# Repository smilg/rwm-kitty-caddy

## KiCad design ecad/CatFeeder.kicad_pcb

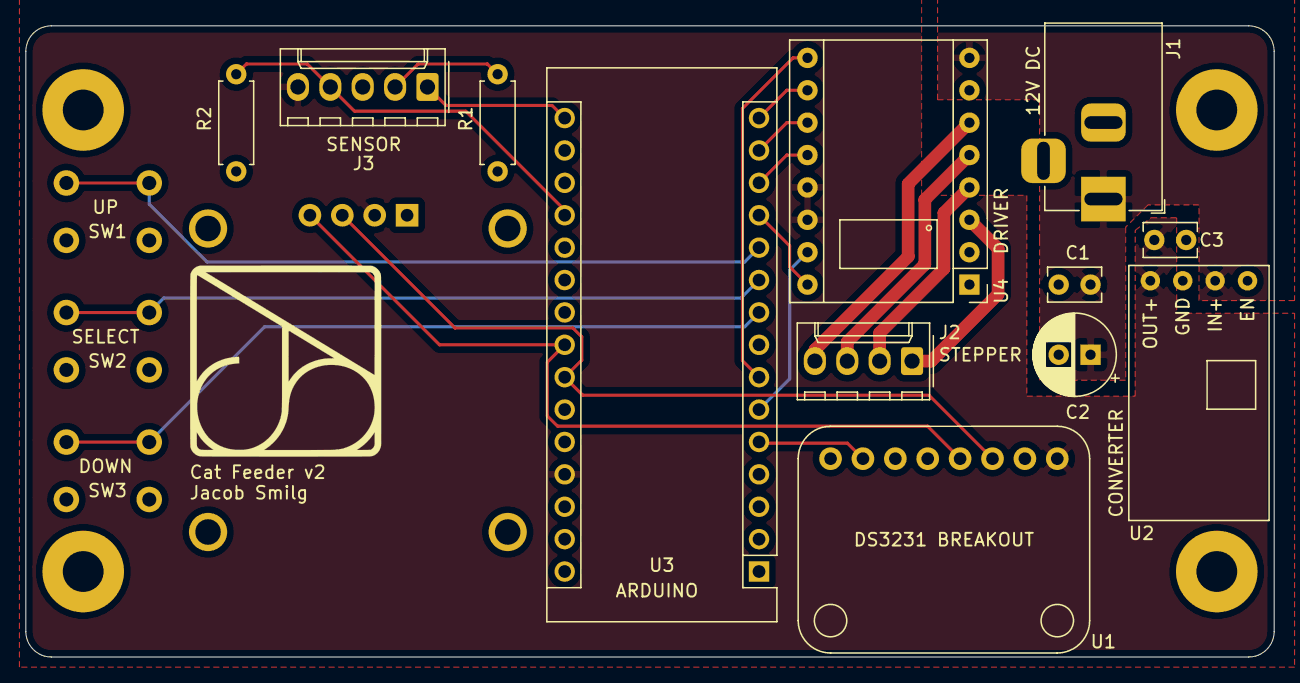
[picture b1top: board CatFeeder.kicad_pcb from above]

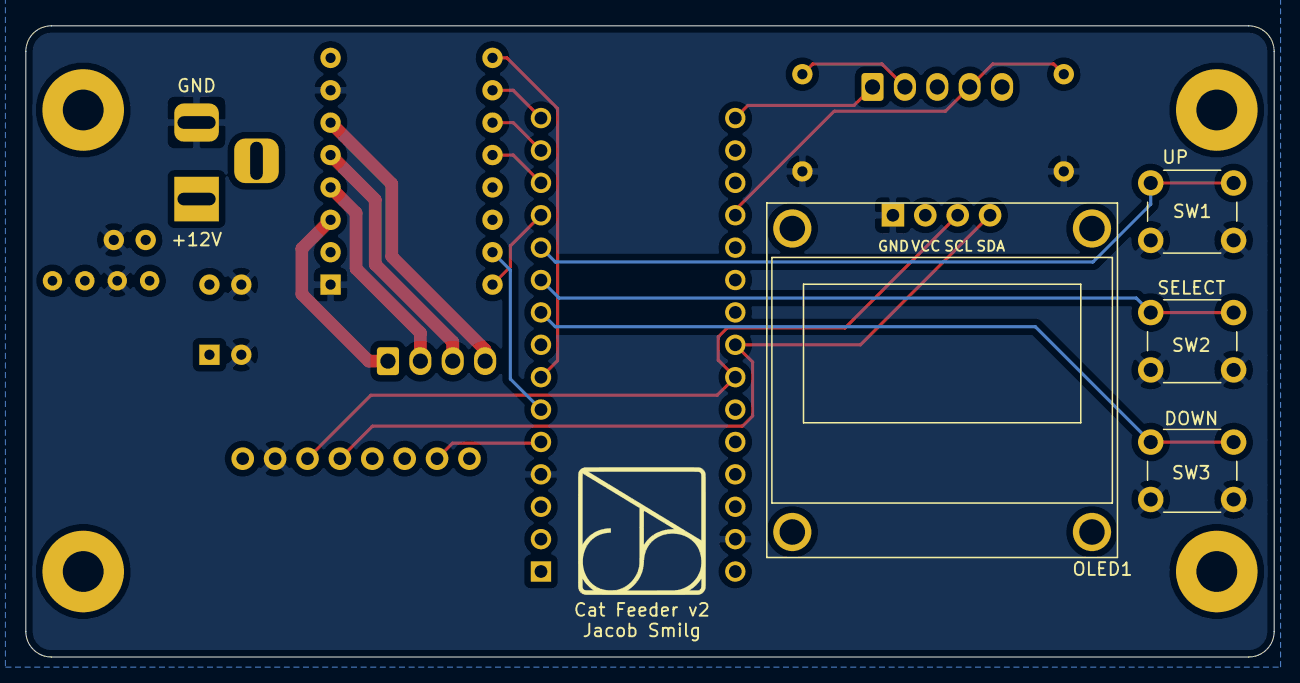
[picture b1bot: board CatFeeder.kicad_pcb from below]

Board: 2 copper layers, 97.9 x 49.5 mm, 16 parts (4 on the bottom side), 22 nets.

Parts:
C1, C3: 0.1μF; C_Rect_L4.0mm_W2.5mm_P2.50mm
C2: 100μF; CP_Radial_D6.3mm_P2.50mm
J1: Barrel_Jack; BarrelJack_Horizontal
J2: STEPPER; Molex_KK-254_AE-6410-04A_1x04_P2.54mm_Vertical
J3: OP740WZ; Molex_KK-254_AE-6410-05A_1x05_P2.54mm_Vertical
OLED1: I2COLEDDisplay; i2cOLED
R1: 100Ω; R_Axial_DIN0207_L6.3mm_D2.5mm_P7.62mm_Horizontal
R2: 100KΩ; R_Axial_DIN0207_L6.3mm_D2.5mm_P7.62mm_Horizontal
SW1: UP; SW_PUSH_6mm
SW2: SELECT; SW_PUSH_6mm
SW3: DOWN; SW_PUSH_6mm
U1: DS3231 BREAKOUT; DS3231Breakout
U2: BuckConverter; BuckConverterBreakout
U3: Arduino_Nano_v3.x; Arduino_Nano
U4: DRV8825; DRV8825Breakout

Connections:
1HZ_INT: U1.7, U3.5
+5V: C3.1, J3.5, OLED1.2, U1.1, U2.1, U3.27, U4.13, U4.14
+12V: C1.1, C2.1, J1.1, U2.3, U4.8
DIR: U3.12, U4.16
DOWN: SW3.2, U3.9
GND: C1.2, C2.2, C3.2, J1.2, OLED1.1, R1.2, R2.2, SW1.1, SW2.1, SW3.1, U1.2, U2.2, U3.4, U3.29, U4.1, U4.7
M0: U3.15, U4.10
M1: U3.14, U4.11
M2: U3.13, U4.12
unnamed: J2.1, U4.3
unnamed: J2.2, U4.4
unnamed: J2.3, U4.5
unnamed: J2.4, U4.6
unnamed: J3.2, R1.1
SCL: OLED1.3, U1.3, U3.24
SDA: OLED1.4, U1.4, U3.23
SELECT: SW2.2, U3.10
SENSOR: J3.4, R2.1, U3.19
SENSOR_ACTIVE: J3.1, U3.16
STEP: U3.6, U4.15
STEPPER_EN: U3.7, U4.9
UP: SW1.2, U3.11

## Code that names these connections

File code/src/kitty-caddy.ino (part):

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#define DEBOUNCE_TIME 100

#define STEP_PIN 3
#define STEPPER_EN_PIN 4
#define DIR_PIN 9
#define MSTEP0_PIN 12
#define MSTEP1_PIN 11
#define MSTEP2_PIN 10

#define SENSOR_ACTIVE_PIN 13
#define SENSOR_IN_PIN A0

// sensor threshold for being in the center of the white mark
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}

void HomeTrays() {
    digitalWrite(SENSOR_ACTIVE_PIN, HIGH);
    delay(15);
    
    stepper.setMaxSpeed(2000);
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    stepper.move(-200);
    stepper.runToPosition();

    digitalWrite(SENSOR_ACTIVE_PIN, LOW);
    current_screen = 0;
}

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    } while(u8g2.nextPage());

    // stepper motor pins
    pinMode(STEPPER_EN_PIN, OUTPUT);
    pinMode(STEP_PIN, OUTPUT);
    pinMode(DIR_PIN, OUTPUT);
    pinMode(MSTEP0_PIN, OUTPUT);
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    pinMode(BTN_SEL, INPUT_PULLUP);
    pinMode(BTN_DOWN, INPUT_PULLUP);

    // homing sensor pin
    pinMode(SENSOR_ACTIVE_PIN, OUTPUT);
    digitalWrite(SENSOR_ACTIVE_PIN, LOW);

    /**
     * microstepping setup - 1/8 step
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    digitalWrite(MSTEP0_PIN, HIGH);
    digitalWrite(MSTEP1_PIN, HIGH);
    digitalWrite(MSTEP2_PIN, LOW);
    digitalWrite(STEPPER_EN_PIN, LOW);

    // rtc init
    URTCLIB_WIRE.begin();
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
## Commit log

2021-12-14 configure .gitignore
2021-12-14 add source code and bitmaps
2021-12-14 add ecad files
2021-12-14 add documentation photos
2021-12-14 add kicad images
2021-12-14 add portfolio writeup
2021-12-14 fix image embeds
2021-12-14 add demo videos
2021-12-14 add demo gifs
2021-12-14 update portfolio writeup
